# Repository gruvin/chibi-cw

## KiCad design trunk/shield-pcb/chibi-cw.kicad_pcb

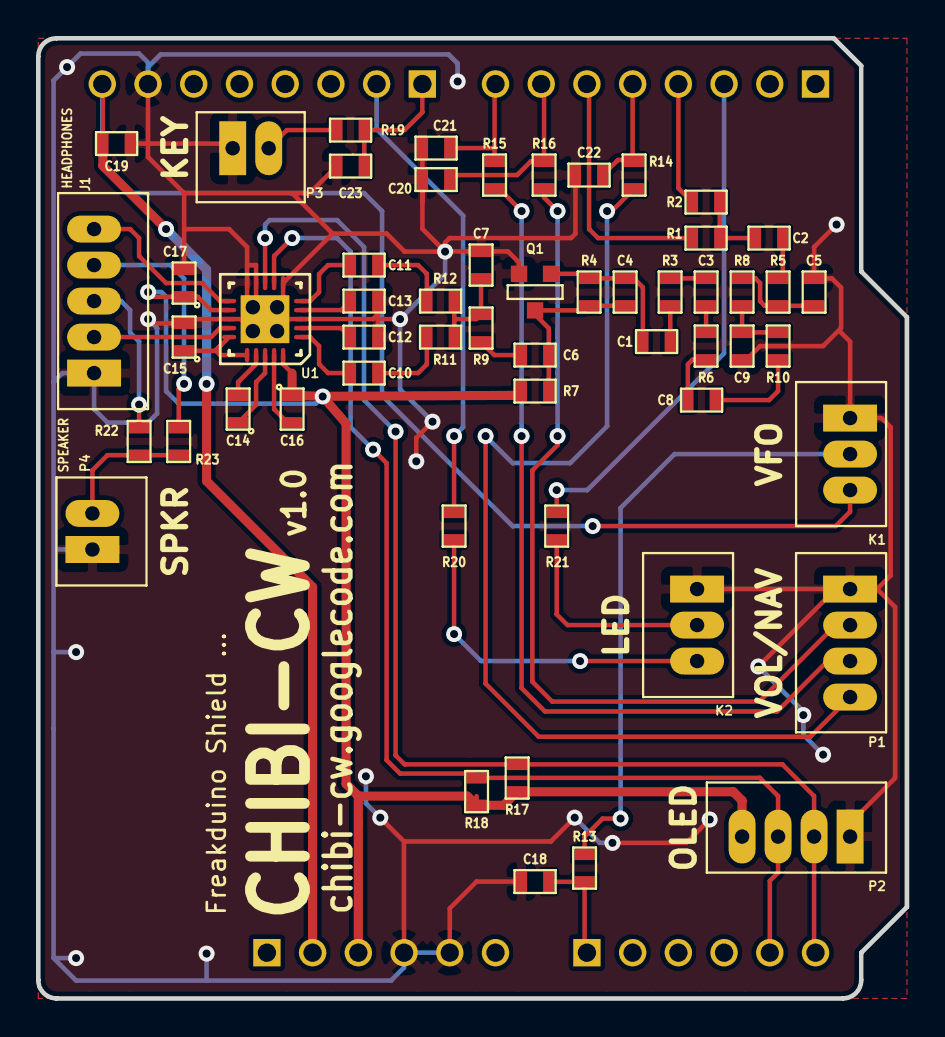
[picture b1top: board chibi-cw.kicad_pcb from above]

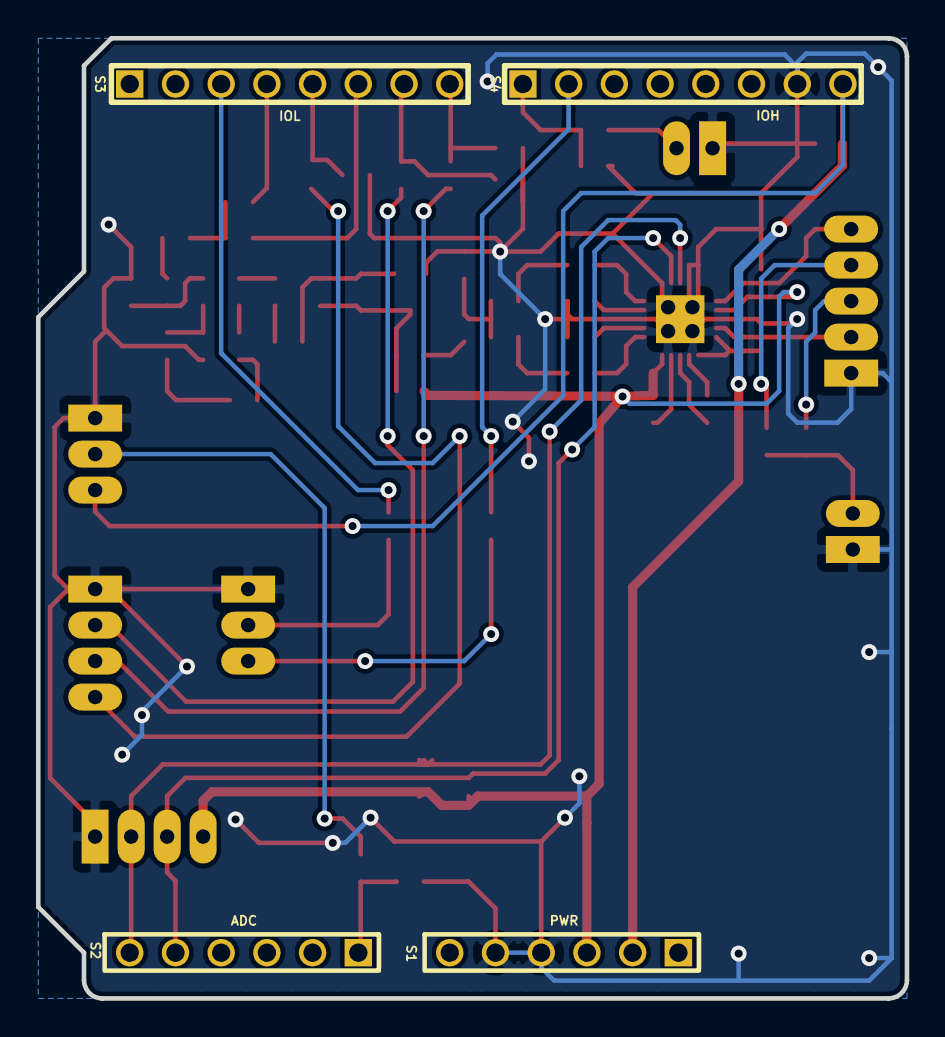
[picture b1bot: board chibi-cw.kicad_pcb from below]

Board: 2 copper layers, 48.3 x 53.3 mm, 59 parts (4 on the bottom side), 49 nets.

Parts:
C1, C2, C6: 2u2; SM0603
C3: 2n2; SM0603
C4, C8, C9: 10n; SM0603
C5, C18, C19, C20, C21, C22, C23: 100n; SM0603
C7: 0u1; SM0603
C10, C11, C12, C13: 470n; SM0603
C14, C15, C16, C17: 1u; SM0603_CPOL
J1: HEADPHONES; CONN_2MM_5x1
K1, K2: CONN_3; CONN_2MM_3x1
P1, P2: CONN_4; CONN_2MM_4x1
P3: CONN_2; CONN_2MM_2x1
P4: SPEAKER; CONN_2MM_2x1
Q1: BC847; SOT23EBC
R1, R2, R17, R18: 2K2; SM0603
R3: 56K; SM0603
R4, R7: 470K; SM0603
R5, R9: 560R; SM0603
R6, R20: 1K5; SM0603
R8: 5K6; SM0603
R10: 15K; SM0603
R11, R12: 10K; SM0603
R13, R14, R15, R16, R19: 200; SM0603
R21: 1K; SM0603
R22, R23: 10R; SM0603
S1: PWR; pin_array_6x1
S2: ADC; pin_array_6x1
S3: IOL; pin_array_8x1
S4: IOH; pin_array_8x1
U1: TPA6130A2; QFN20

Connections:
3.3V: C19.2, K1.3, S1.2, S4.8
5V: C16.1, C17.1, P2.4, R7.2, R17.2, R18.2, S1.3, U1.12, U1.20
AD0: C18.2, R13.1, S2.1
AD4/SDA: P2.3, R18.1, S2.5, U1.7
AD5/SCL: P2.2, R17.1, S2.6, U1.8
GND: C5.1, C7.2, C9.1, C12.1, C13.1, C15.2, C17.2, C18.1, C19.1, C20.1, C21.1, C22.1, C23.1, J1.1, K1.1, K2.1, P1.1, P2.1, P3.1, P4.1, Q1.1, S1.4, S1.5, S4.7, U1.3, U1.6, U1.9, U1.10, U1.13
IO2: R21.1, S3.3
IO3: R2.1, S3.4
IO4: C22.2, R14.1, S3.5
IO5: R1.1, S3.6
IO6: C20.2, R16.1, S3.7
IO7: C21.2, R15.1, S3.8
IO8: C23.2, R19.1, S4.1
IO9: R20.1, S4.2
unnamed: K1.2, R13.2
unnamed: C1.2, C4.1, Q1.2, R4.1
unnamed: P1.2, R16.2
unnamed: P1.4, R14.2
unnamed: P1.3, R15.2
unnamed: C15.1, U1.15, U1.16
unnamed: C13.2, U1.4
unnamed: C11.2, U1.5
unnamed: C11.1, R12.2
unnamed: C12.2, U1.2
unnamed: C10.2, U1.1
unnamed: C10.1, R11.2
unnamed: J1.2, U1.14
unnamed: J1.5, U1.11
unnamed: C6.2, R9.2
unnamed: C2.1, R1.2, R2.2
unnamed: C7.1, R9.1, R11.1, R12.1
unnamed: K2.2, R21.2
unnamed: K2.3, R20.2
unnamed: P3.2, R19.2
unnamed: P4.2, R22.2, R23.2
unnamed: J1.4, R23.1
unnamed: J1.3, R22.1
unnamed: C2.2, R5.1
unnamed: C1.1, R3.2
unnamed: C3.1, R3.1
unnamed: C8.1, R6.2
unnamed: C3.2, R6.1
unnamed: C9.2, R8.2, R10.2
unnamed: C8.2, R10.1
unnamed: C5.2, R5.2, R8.1
unnamed: C14.1, U1.18
unnamed: C14.2, U1.17
unnamed: C16.2, U1.19
unnamed: C4.2, C6.1, Q1.3, R4.2, R7.1

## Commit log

2013-08-04 Initial directory structure.
2013-08-04 wiki image
2013-08-04 wiki image fix
2013-08-04 Added KEY silk label
2013-08-04 Updated scematic revision number (from 0.2 to 1.0)
2013-08-05 3D connector parts improved (more accurate size etc)
2013-08-05 wiki image update
2013-08-05 Production files produced and given the eye in Gerbview. Looking OK.
2013-08-05 Minor improvements to JST XH 2.0 connector 3D models.
2013-08-06 image update
2013-08-06 svn password storage test
2013-08-06 svn password storage test 2
2013-08-06 Trivial changes, here and there.
2013-08-21 Began oLED display support.
    A frequency of sorts is displayed on the top line.
    TX and RX spot lines are on pages 2 and 3 (2nd line top and bottom halves), respectively.
    "Chibi-CW" appears also, centered on the bottom line.
2013-08-21 Comment correction / removal.
2013-08-21 Comments only
2013-08-21 + Moved 16x16 font date to PROGMEM space. + Modified the Kozig ZT oLED library to accomodate PROGMEN for the one function I'm currently using. + Added modified Kozig ZT OLED library to repository.
2013-08-22 + Enhanced digital protocol now used identitification header byte 0xCC to help filter junk data on the (real) frequency. + New protocol also includes trx of callsigns. These are hard coded but will b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
2013-08-22 oLED delays for better stability of callsign display and erase
2013-08-22 Added (same) identifier byte at end of packet as well.
2013-08-23 + Added chibi serial port commands 'setcall' and 'getcall', to set or get the radio's callsign, respectively. + Increased maxium callsign length to 16 (the full width of the display.)
2013-08-23 trivial
2013-08-23 trivial comment fixes
2013-10-28 PCB final check-over OK. Created production files. (Will freeze.)
2013-10-28 PCB v1.00 tagged (frozen) for production
    Misc other files added.
2013-10-28 PCB: Just added dimensioning notes to drawings layer.
2013-11-07 Wiki image added.
2013-11-10 Added silk screen parts layout imgage.
2013-11-11 Added I2C audio amp chip initialisation code to firmware. Seems to be working fine. The chip appear to completely refuse to drive my 8-ohm speaker through the two 10-ohm resistors. *shrug*
    (+ Trival part reference position move in schematic.)
2013-11-11 Added wiki image
2014-02-11 Added Maple JTAG adapteri PCB, to get Gerber files for ITead, because I'm too lazy nowadays to fab my own simple boards. :-P
    Based on Eagle version, referenced from http://wiki.leaflabs.com/index.php?title=Maple_JTAG_How_To
2014-02-11 Added JTAG adapter board dimensions and Gerber ZIP file.
2015-03-15 Migrating wiki contents from Google Code
